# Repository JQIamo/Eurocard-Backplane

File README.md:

# Eurocard-Backplane

A customized backplane for the JQI Eurocard racks.

This repository also includes a "starter" schematic/board for compliant modules: `EurocardModule.*` Simply copy and paste this into your project folder (or re-save with a different name into your project), and you're off to the races!

## JQI Eurocard standard

We have made our backplane standard compliant with the Toptica backplane -- ie, Toptica modules should work in the JQI rack (and vice versa). However, double-check to make sure there aren't conflicting GPIO signal lines!

Compliant modules should follow the backplane standard (see link below to backplane pinout, or check out the starter schematic in this repository). Here are a few other guidlines that should be followed when designing new modules:

* You are responsible for regulating down from `+/-15V` to the voltages you need.
* De-couple your module from the backplane power traces (eg, with a ferrite bead); be careful about introducing additional noise.
* The standard power supply should provide ~ 7 (?) amps of current to the rack at both `+15V` and `-15V`
* If you need higher voltages, use the HV line.
* The backplane will be (!) equipped with a microcontroller and `WIZNET` ethernet adapter.
* SPI chip-select lines (`SPI_CS`) are routed to individual modules (ie, not tied together on the back plane). If you want to use a microcontroller, you can communicate with the backplane MCU this way. You can also use the I2C bus if you wish (`I2C_SDA` and `I2C_SCL`).
* There is a 5V stable reference, provided from an LM399H zener reference on the back plane.

**Resources**:

* [Backplane pinout](https://docs.google.com/spreadsheets/d/1GiwGvO8Z4_M1yfA_NvQcPyxT0hQa0t4iZVfY6wiVYis/edit?usp=sharing)
* ...

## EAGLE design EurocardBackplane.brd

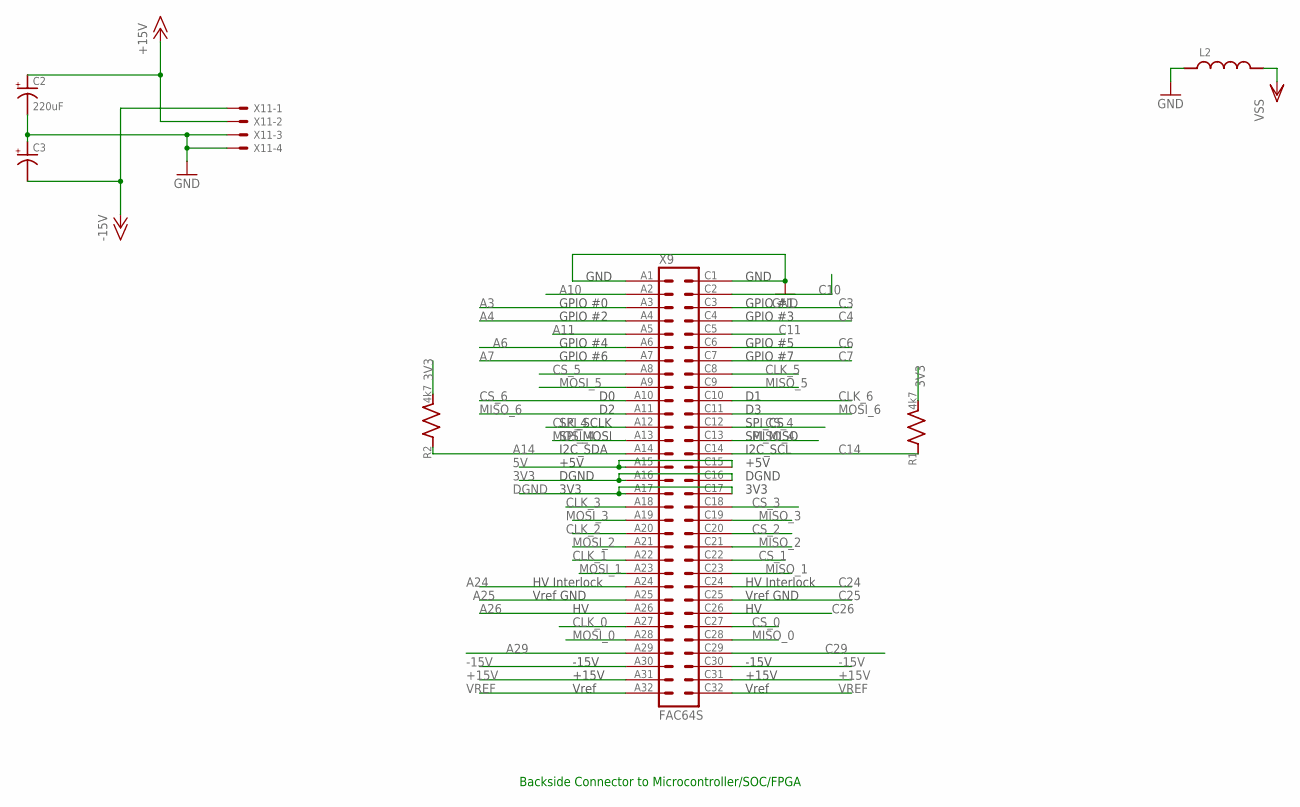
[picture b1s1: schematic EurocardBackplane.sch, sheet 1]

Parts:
C2: 220uF; PANASONIC_F
C3: C_POL_SMDF; PANASONIC_F
L2: L_FERRITE_SMDLFERRITE_0805; R_0805
R1, R2: 4k7; R_0603
X9: FAC64S
X11: 5566-4

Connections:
3V3: R1.P$2 (2), R2.P$2 (2), X9.A16, X9.C16; also elsewhere on the board
5V: X9.A15, X9.C15; also elsewhere on the board
+15V: C2.+, X9.A31, X9.C31, X11.2; also elsewhere on the board
-15V: C3.-, X9.A30, X9.C30, X11.1; also elsewhere on the board
A3: X9.A3; also elsewhere on the board
A4: X9.A4; also elsewhere on the board
A6: X9.A6; also elsewhere on the board
A7: X9.A7; also elsewhere on the board
A10: X9.A2; also elsewhere on the board
A11: X9.A5; also elsewhere on the board
A14: R2.P$1 (1), X9.A14; also elsewhere on the board
A24: X9.A24; also elsewhere on the board
A25: X9.A25; also elsewhere on the board
A26: X9.A26; also elsewhere on the board
A29: X9.A29; also elsewhere on the board
C3: X9.C3; also elsewhere on the board
C4: X9.C4; also elsewhere on the board
C6: X9.C6; also elsewhere on the board
C7: X9.C7; also elsewhere on the board
C10: X9.C2; also elsewhere on the board
C11: X9.C5; also elsewhere on the board
C14: R1.P$1 (1), X9.C14; also elsewhere on the board
C24: X9.C24; also elsewhere on the board
C25: X9.C25; also elsewhere on the board
C26: X9.C26; also elsewhere on the board
C29: X9.C29; also elsewhere on the board
CLK_0: X9.A27; also elsewhere on the board
CLK_1: X9.A22; also elsewhere on the board
CLK_2: X9.A20; also elsewhere on the board
CLK_3: X9.A18; also elsewhere on the board
CLK_4: X9.A12; also elsewhere on the board
CLK_5: X9.C8; also elsewhere on the board
CLK_6: X9.C10; also elsewhere on the board
CS_0: X9.C27; also elsewhere on the board
CS_1: X9.C22; also elsewhere on the board
CS_2: X9.C20; also elsewhere on the board
CS_3: X9.C18; also elsewhere on the board
CS_4: X9.C12; also elsewhere on the board
CS_5: X9.A8; also elsewhere on the board
CS_6: X9.A10; also elsewhere on the board
DGND: X9.A17, X9.C17; also elsewhere on the board
GND: C2.-, C3.+, L2.P$1 (1), X9.A1, X9.C1, X11.3, X11.4; also elsewhere on the board
MISO_0: X9.C28; also elsewhere on the board
MISO_1: X9.C23; also elsewhere on the board
MISO_2: X9.C21; also elsewhere on the board
MISO_3: X9.C19; also elsewhere on the board
MISO_4: X9.C13; also elsewhere on the board
MISO_5: X9.C9; also elsewhere on the board
MISO_6: X9.A11; also elsewhere on the board
MOSI_0: X9.A28; also elsewhere on the board
MOSI_1: X9.A23; also elsewhere on the board
MOSI_2: X9.A21; also elsewhere on the board
MOSI_3: X9.A19; also elsewhere on the board
MOSI_4: X9.A13; also elsewhere on the board
MOSI_5: X9.A9; also elsewhere on the board
MOSI_6: X9.C11; also elsewhere on the board
VREF: X9.A32, X9.C32
VSS: L2.P$2 (2)

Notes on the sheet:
Backside Connector to Microcontroller/SOC/FPGA

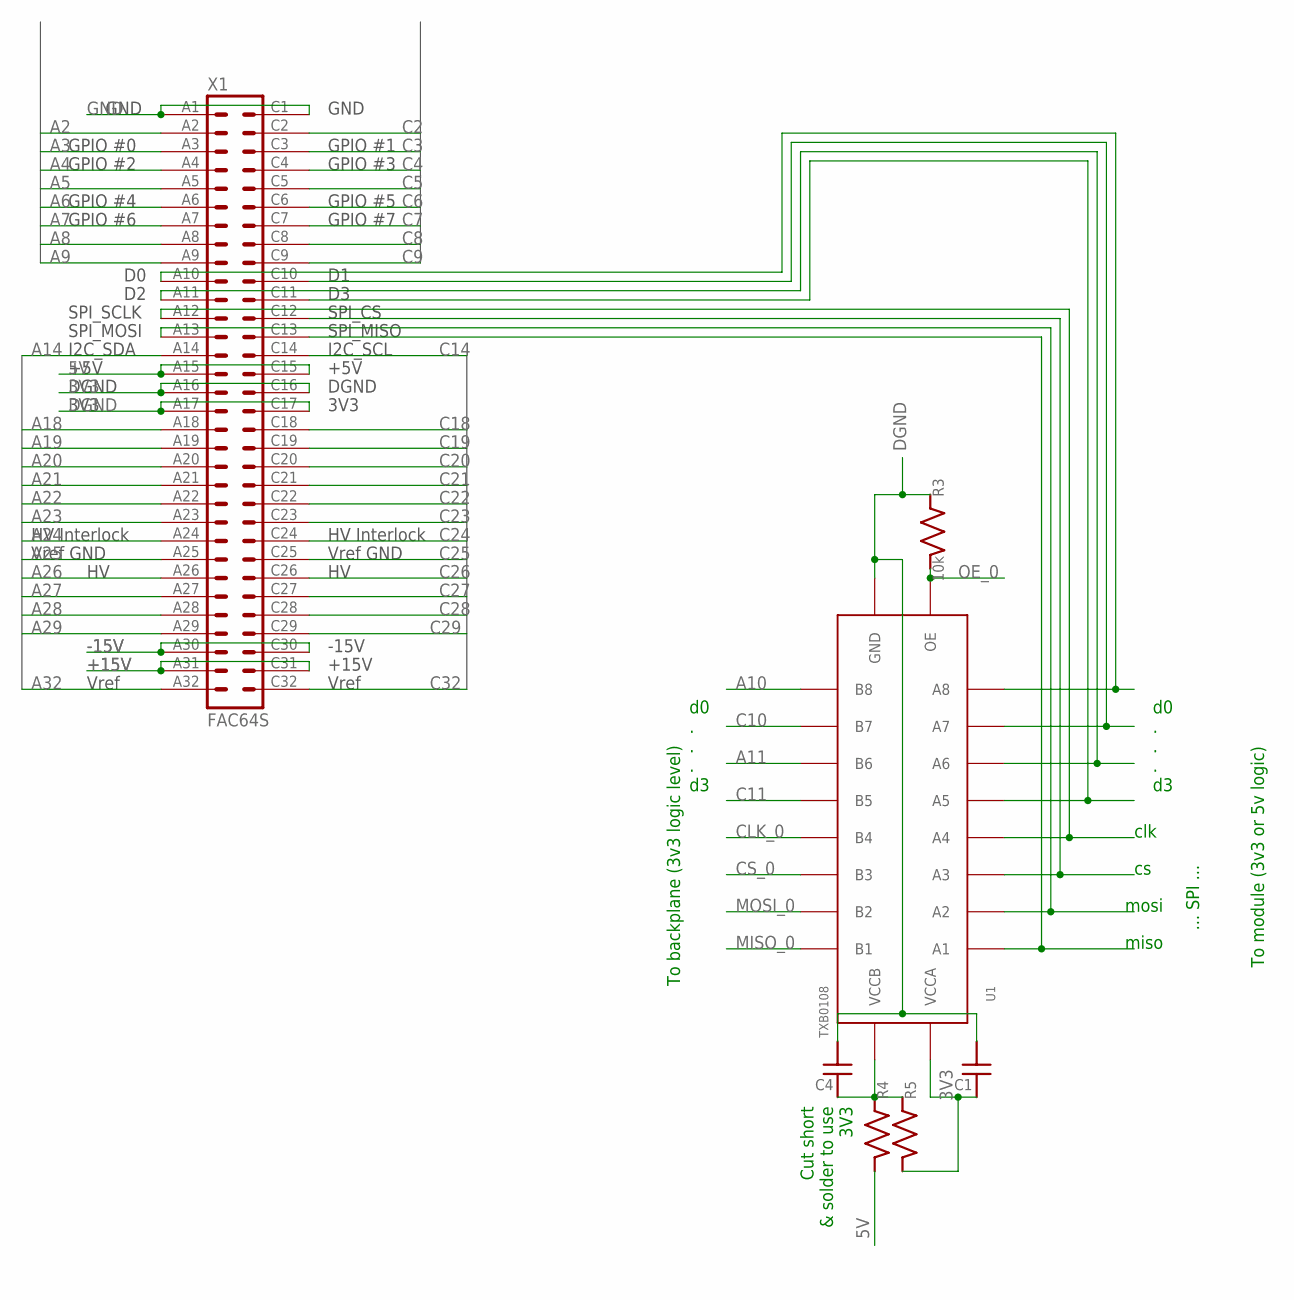
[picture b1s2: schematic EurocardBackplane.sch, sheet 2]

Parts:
C1, C4: C_MLCC_SMDCMLCC_0603; C_MLCC_0603
R3: 10k; R_0603
R4, R5: R_SMDR0603; R_0603
U1: TXB0108; TSSOP20
X1: FAC64S

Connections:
3V3: C1.P$1 (1), R5.P$2 (2), U1.2 (VCCA), X1.A16, X1.C16; also elsewhere on the board
5V: R4.P$2 (2), X1.A15, X1.C15; also elsewhere on the board
+15V: X1.A31, X1.C31; also elsewhere on the board
-15V: X1.A30, X1.C30; also elsewhere on the board
A2: X1.A2; also elsewhere on the board
A3: X1.A3; also elsewhere on the board
A4: X1.A4; also elsewhere on the board
A5: X1.A5; also elsewhere on the board
A6: X1.A6; also elsewhere on the board
A7: X1.A7; also elsewhere on the board
A8: X1.A8; also elsewhere on the board
A9: X1.A9; also elsewhere on the board
A10: U1.12 (B8); also elsewhere on the board
A11: U1.14 (B6); also elsewhere on the board
A14: X1.A14; also elsewhere on the board
A18: X1.A18; also elsewhere on the board
A19: X1.A19; also elsewhere on the board
A20: X1.A20; also elsewhere on the board
A21: X1.A21; also elsewhere on the board
A22: X1.A22; also elsewhere on the board
A23: X1.A23; also elsewhere on the board
A24: X1.A24; also elsewhere on the board
A25: X1.A25; also elsewhere on the board
A26: X1.A26; also elsewhere on the board
A27: X1.A27; also elsewhere on the board
A28: X1.A28; also elsewhere on the board
A29: X1.A29; also elsewhere on the board
A32: X1.A32; also elsewhere on the board
C2: X1.C2; also elsewhere on the board
C3: X1.C3; also elsewhere on the board
C4: X1.C4; also elsewhere on the board
C5: X1.C5; also elsewhere on the board
C6: X1.C6; also elsewhere on the board
C7: X1.C7; also elsewhere on the board
C8: X1.C8; also elsewhere on the board
C9: X1.C9; also elsewhere on the board
C10: U1.13 (B7); also elsewhere on the board
C11: U1.15 (B5); also elsewhere on the board
C14: X1.C14; also elsewhere on the board
C18: X1.C18; also elsewhere on the board
C19: X1.C19; also elsewhere on the board
C20: X1.C20; also elsewhere on the board
C21: X1.C21; also elsewhere on the board
C22: X1.C22; also elsewhere on the board
C23: X1.C23; also elsewhere on the board
C24: X1.C24; also elsewhere on the board
C25: X1.C25; also elsewhere on the board
C26: X1.C26; also elsewhere on the board
C27: X1.C27; also elsewhere on the board
C28: X1.C28; also elsewhere on the board
C29: X1.C29; also elsewhere on the board
C32: X1.C32; also elsewhere on the board
CLK_0: U1.16 (B4); also elsewhere on the board
CS_0: U1.17 (B3); also elsewhere on the board
DGND: C1.P$2 (2), C4.P$2 (2), R3.P$1 (1), U1.11 (GND), X1.A17, X1.C17; also elsewhere on the board
GND: X1.A1, X1.C1; also elsewhere on the board
MISO_0: U1.20 (B1); also elsewhere on the board
MOSI_0: U1.18 (B2); also elsewhere on the board
unnamed: U1.9 (A8), X1.A10
unnamed: U1.8 (A7), X1.C10
unnamed: U1.7 (A6), X1.A11
unnamed: U1.6 (A5), X1.C11
unnamed: U1.5 (A4), X1.A12
unnamed: U1.4 (A3), X1.C12
unnamed: U1.3 (A2), X1.A13
unnamed: U1.1 (A1), X1.C13
unnamed: C4.P$1 (1), R4.P$1 (1), R5.P$1 (1), U1.19 (VCCB)
OE_0: R3.P$2 (2), U1.10 (OE)

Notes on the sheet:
d0 . . . d3
To backplane (3v3 logic level)
To module (3v3 or 5v logic)
clk
mosi
miso
... SPI ...
Cut short & solder to use 3V3

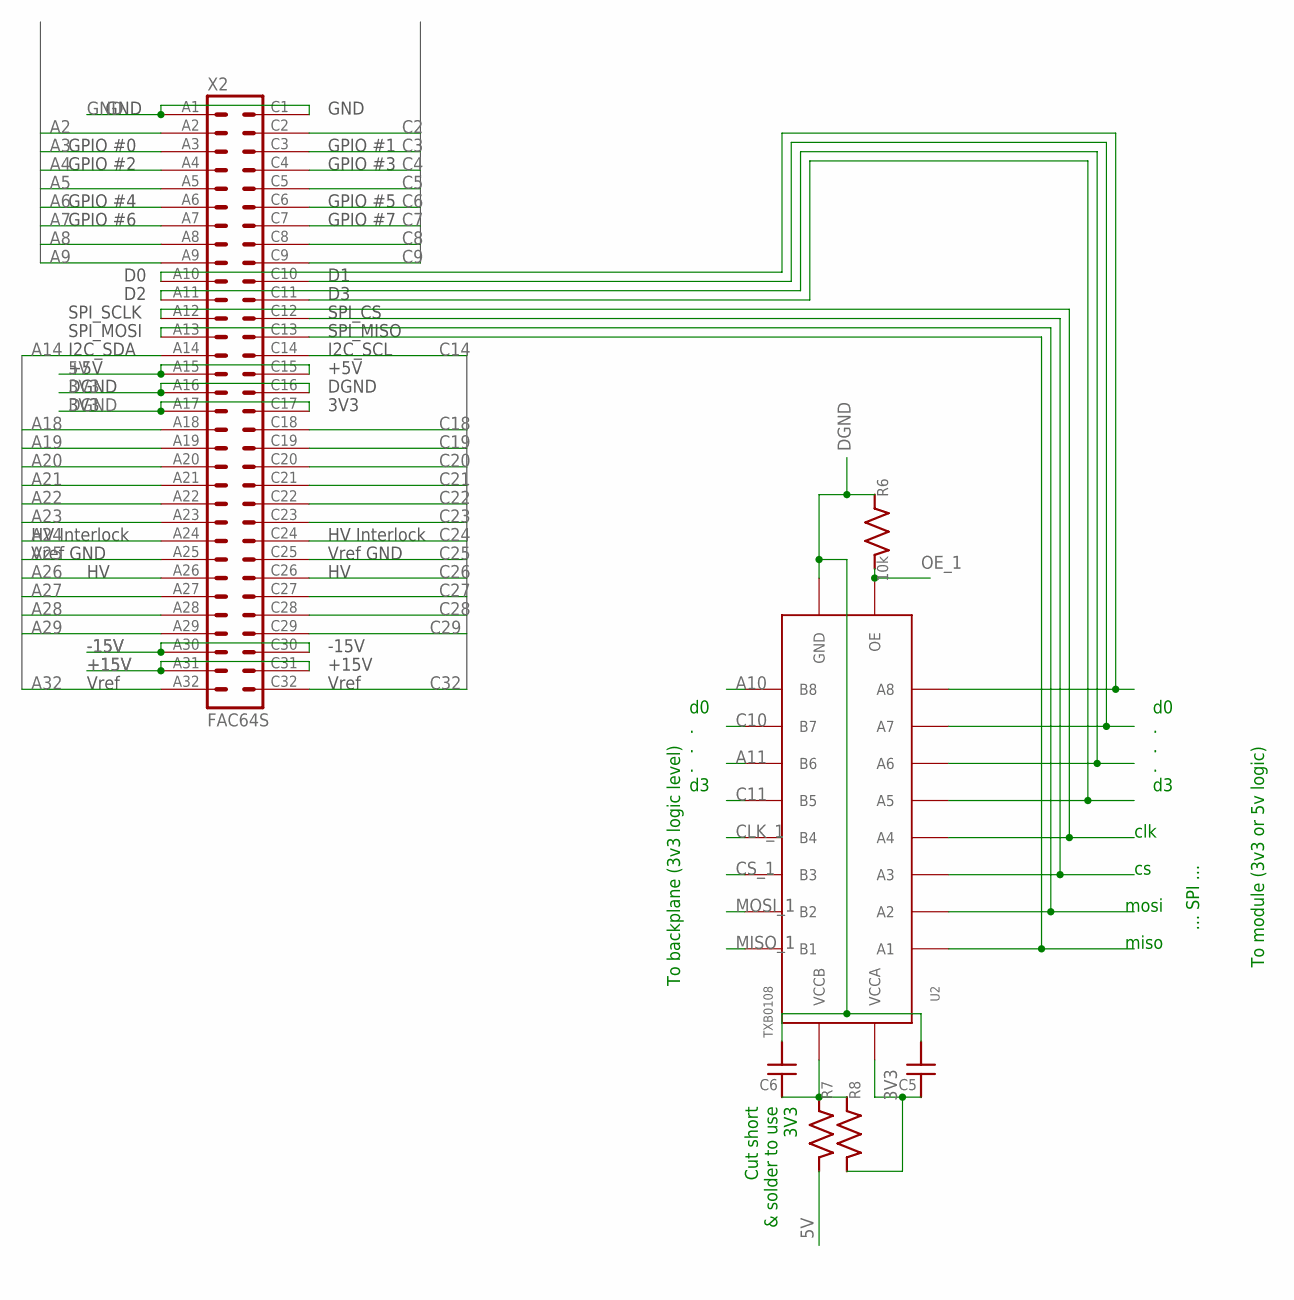
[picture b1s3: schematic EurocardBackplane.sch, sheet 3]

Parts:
C5, C6: C_MLCC_SMDCMLCC_0603; C_MLCC_0603
R6: 10k; R_0603
R7, R8: R_SMDR0603; R_0603
U2: TXB0108; TSSOP20
X2: FAC64S

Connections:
3V3: C5.P$1 (1), R8.P$2 (2), U2.2 (VCCA), X2.A16, X2.C16; also elsewhere on the board
5V: R7.P$2 (2), X2.A15, X2.C15; also elsewhere on the board
+15V: X2.A31, X2.C31; also elsewhere on the board
-15V: X2.A30, X2.C30; also elsewhere on the board
A2: X2.A2; also elsewhere on the board
A3: X2.A3; also elsewhere on the board
A4: X2.A4; also elsewhere on the board
A5: X2.A5; also elsewhere on the board
A6: X2.A6; also elsewhere on the board
A7: X2.A7; also elsewhere on the board
A8: X2.A8; also elsewhere on the board
A9: X2.A9; also elsewhere on the board
A10: U2.12 (B8); also elsewhere on the board
A11: U2.14 (B6); also elsewhere on the board
A14: X2.A14; also elsewhere on the board
A18: X2.A18; also elsewhere on the board
A19: X2.A19; also elsewhere on the board
A20: X2.A20; also elsewhere on the board
A21: X2.A21; also elsewhere on the board
A22: X2.A22; also elsewhere on the board
A23: X2.A23; also elsewhere on the board
A24: X2.A24; also elsewhere on the board
A25: X2.A25; also elsewhere on the board
A26: X2.A26; also elsewhere on the board
A27: X2.A27; also elsewhere on the board
A28: X2.A28; also elsewhere on the board
A29: X2.A29; also elsewhere on the board
A32: X2.A32; also elsewhere on the board
C2: X2.C2; also elsewhere on the board
C3: X2.C3; also elsewhere on the board
C4: X2.C4; also elsewhere on the board
C5: X2.C5; also elsewhere on the board
C6: X2.C6; also elsewhere on the board
C7: X2.C7; also elsewhere on the board
C8: X2.C8; also elsewhere on the board
C9: X2.C9; also elsewhere on the board
C10: U2.13 (B7); also elsewhere on the board
C11: U2.15 (B5); also elsewhere on the board
C14: X2.C14; also elsewhere on the board
C18: X2.C18; also elsewhere on the board
C19: X2.C19; also elsewhere on the board
C20: X2.C20; also elsewhere on the board
C21: X2.C21; also elsewhere on the board
C22: X2.C22; also elsewhere on the board
C23: X2.C23; also elsewhere on the board
C24: X2.C24; also elsewhere on the board
C25: X2.C25; also elsewhere on the board
C26: X2.C26; also elsewhere on the board
C27: X2.C27; also elsewhere on the board
C28: X2.C28; also elsewhere on the board
C29: X2.C29; also elsewhere on the board
C32: X2.C32; also elsewhere on the board
CLK_1: U2.16 (B4); also elsewhere on the board
CS_1: U2.17 (B3); also elsewhere on the board
DGND: C5.P$2 (2), C6.P$2 (2), R6.P$1 (1), U2.11 (GND), X2.A17, X2.C17; also elsewhere on the board
GND: X2.A1, X2.C1; also elsewhere on the board
MISO_1: U2.20 (B1); also elsewhere on the board
MOSI_1: U2.18 (B2); also elsewhere on the board
unnamed: U2.9 (A8), X2.A10
unnamed: U2.8 (A7), X2.C10
unnamed: U2.7 (A6), X2.A11
unnamed: U2.6 (A5), X2.C11
unnamed: U2.5 (A4), X2.A12
unnamed: U2.4 (A3), X2.C12
unnamed: U2.3 (A2), X2.A13
unnamed: U2.1 (A1), X2.C13
unnamed: C6.P$1 (1), R7.P$1 (1), R8.P$1 (1), U2.19 (VCCB)
OE_1: R6.P$2 (2), U2.10 (OE)

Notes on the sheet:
d0 . . . d3
To backplane (3v3 logic level)
To module (3v3 or 5v logic)
clk
mosi
miso
... SPI ...
Cut short & solder to use 3V3

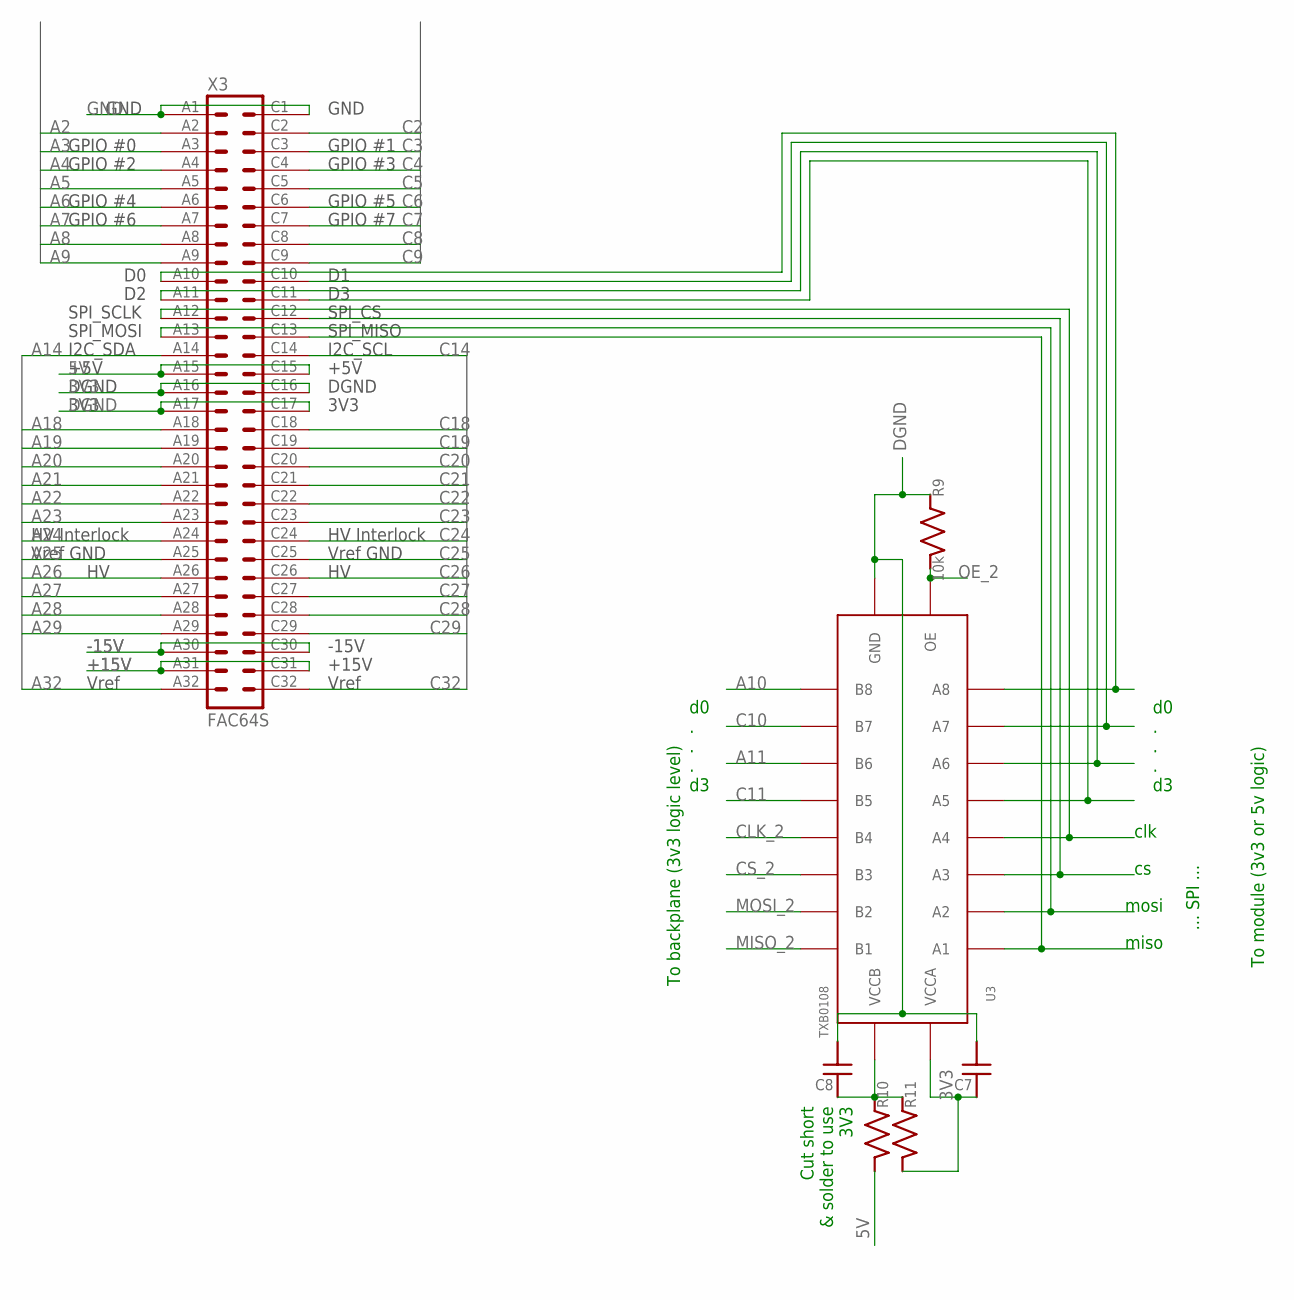
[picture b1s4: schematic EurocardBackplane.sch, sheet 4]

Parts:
C7, C8: C_MLCC_SMDCMLCC_0603; C_MLCC_0603
R9: 10k; R_0603
R10, R11: R_SMDR0603; R_0603
U3: TXB0108; TSSOP20
X3: FAC64S

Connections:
3V3: C7.P$1 (1), R11.P$2 (2), U3.2 (VCCA), X3.A16, X3.C16; also elsewhere on the board
5V: R10.P$2 (2), X3.A15, X3.C15; also elsewhere on the board
+15V: X3.A31, X3.C31; also elsewhere on the board
-15V: X3.A30, X3.C30; also elsewhere on the board
A2: X3.A2; also elsewhere on the board
A3: X3.A3; also elsewhere on the board
A4: X3.A4; also elsewhere on the board
A5: X3.A5; also elsewhere on the board
A6: X3.A6; also elsewhere on the board
A7: X3.A7; also elsewhere on the board
A8: X3.A8; also elsewhere on the board
A9: X3.A9; also elsewhere on the board
A10: U3.12 (B8); also elsewhere on the board
A11: U3.14 (B6); also elsewhere on the board
A14: X3.A14; also elsewhere on the board
A18: X3.A18; also elsewhere on the board
A19: X3.A19; also elsewhere on the board
A20: X3.A20; also elsewhere on the board
A21: X3.A21; also elsewhere on the board
A22: X3.A22; also elsewhere on the board
A23: X3.A23; also elsewhere on the board
A24: X3.A24; also elsewhere on the board
A25: X3.A25; also elsewhere on the board
A26: X3.A26; also elsewhere on the board
A27: X3.A27; also elsewhere on the board
A28: X3.A28; also elsewhere on the board
A29: X3.A29; also elsewhere on the board
A32: X3.A32; also elsewhere on the board
C2: X3.C2; also elsewhere on the board
C3: X3.C3; also elsewhere on the board
C4: X3.C4; also elsewhere on the board
C5: X3.C5; also elsewhere on the board
C6: X3.C6; also elsewhere on the board
C7: X3.C7; also elsewhere on the board
C8: X3.C8; also elsewhere on the board
C9: X3.C9; also elsewhere on the board
C10: U3.13 (B7); also elsewhere on the board
C11: U3.15 (B5); also elsewhere on the board
C14: X3.C14; also elsewhere on the board
C18: X3.C18; also elsewhere on the board
C19: X3.C19; also elsewhere on the board
C20: X3.C20; also elsewhere on the board
C21: X3.C21; also elsewhere on the board
C22: X3.C22; also elsewhere on the board
C23: X3.C23; also elsewhere on the board
C24: X3.C24; also elsewhere on the board
C25: X3.C25; also elsewhere on the board
C26: X3.C26; also elsewhere on the board
C27: X3.C27; also elsewhere on the board
C28: X3.C28; also elsewhere on the board
C29: X3.C29; also elsewhere on the board
C32: X3.C32; also elsewhere on the board
CLK_2: U3.16 (B4); also elsewhere on the board
CS_2: U3.17 (B3); also elsewhere on the board
DGND: C7.P$2 (2), C8.P$2 (2), R9.P$1 (1), U3.11 (GND), X3.A17, X3.C17; also elsewhere on the board
GND: X3.A1, X3.C1; also elsewhere on the board
MISO_2: U3.20 (B1); also elsewhere on the board
MOSI_2: U3.18 (B2); also elsewhere on the board
unnamed: U3.9 (A8), X3.A10
unnamed: U3.8 (A7), X3.C10
unnamed: U3.7 (A6), X3.A11
unnamed: U3.6 (A5), X3.C11
unnamed: U3.5 (A4), X3.A12
unnamed: U3.4 (A3), X3.C12
unnamed: U3.3 (A2), X3.A13
unnamed: U3.1 (A1), X3.C13
unnamed: C8.P$1 (1), R10.P$1 (1), R11.P$1 (1), U3.19 (VCCB)
OE_2: R9.P$2 (2), U3.10 (OE)

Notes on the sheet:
d0 . . . d3
To backplane (3v3 logic level)
To module (3v3 or 5v logic)
clk
mosi
miso
... SPI ...
Cut short & solder to use 3V3

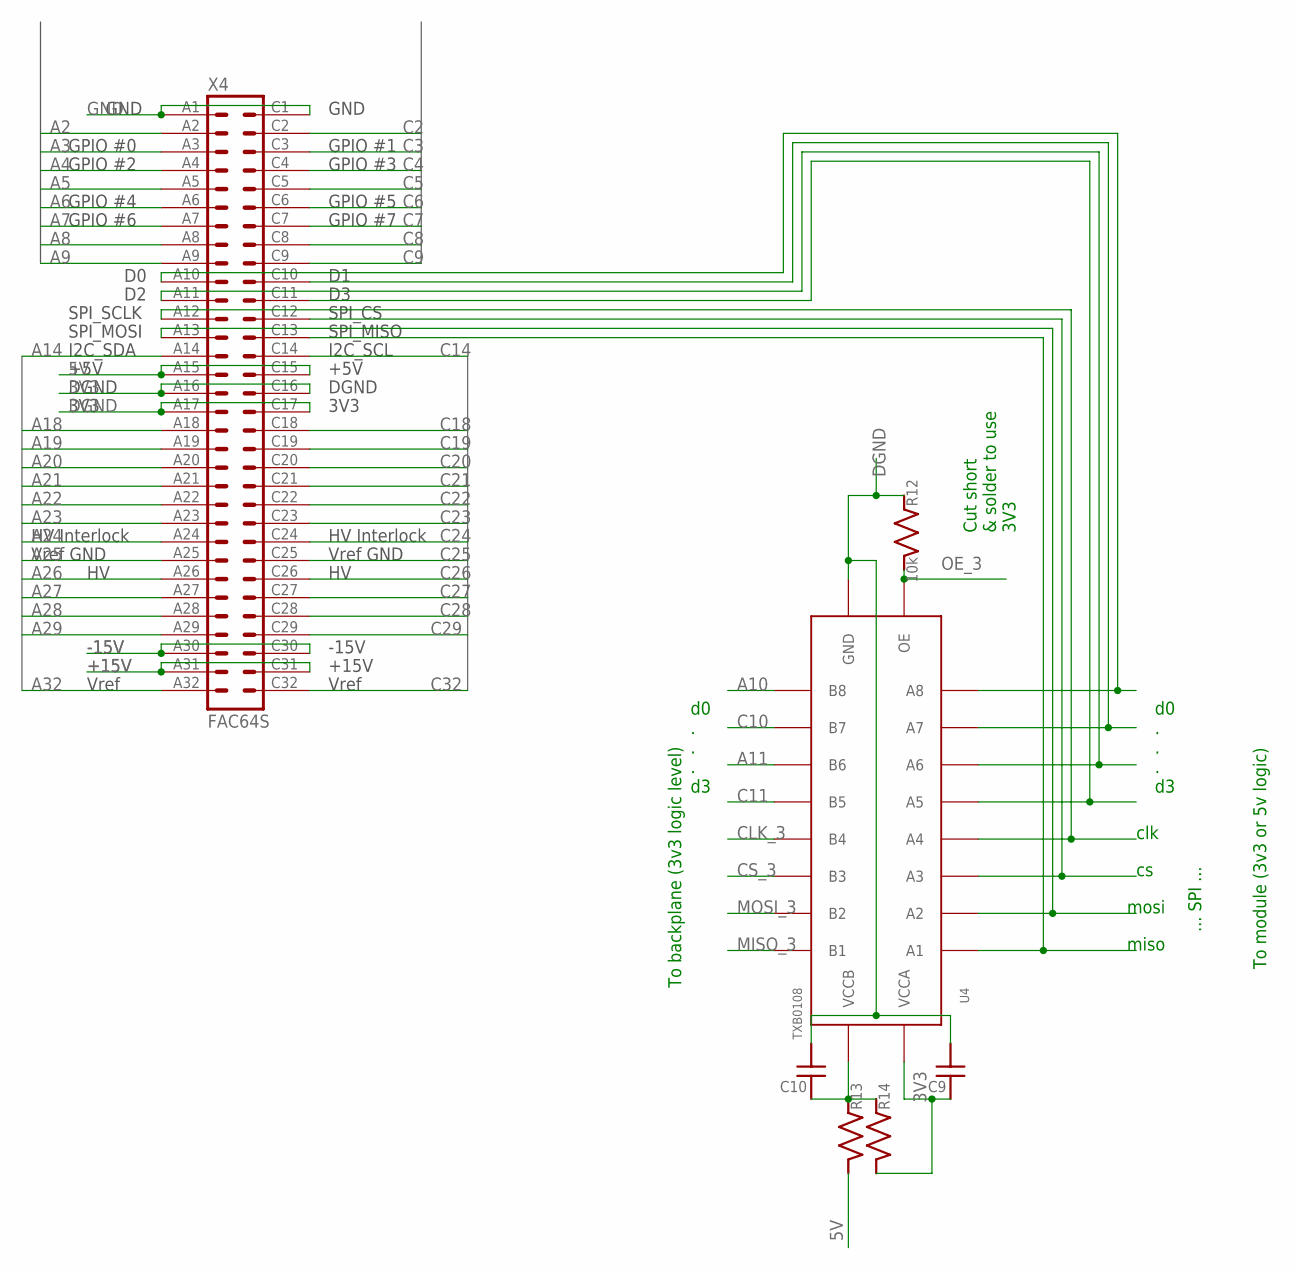
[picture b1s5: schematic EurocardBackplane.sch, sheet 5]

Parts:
C9, C10: C_MLCC_SMDCMLCC_0603; C_MLCC_0603
R12: 10k; R_0603
R13, R14: R_SMDR0603; R_0603
U4: TXB0108; TSSOP20
X4: FAC64S

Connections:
3V3: C9.P$1 (1), R14.P$2 (2), U4.2 (VCCA), X4.A16, X4.C16; also elsewhere on the board
5V: R13.P$2 (2), X4.A15, X4.C15; also elsewhere on the board
+15V: X4.A31, X4.C31; also elsewhere on the board
-15V: X4.A30, X4.C30; also elsewhere on the board
A2: X4.A2; also elsewhere on the board
A3: X4.A3; also elsewhere on the board
A4: X4.A4; also elsewhere on the board
A5: X4.A5; also elsewhere on the board
A6: X4.A6; also elsewhere on the board
A7: X4.A7; also elsewhere on the board
A8: X4.A8; also elsewhere on the board
A9: X4.A9; also elsewhere on the board
A10: U4.12 (B8); also elsewhere on the board
A11: U4.14 (B6); also elsewhere on the board
A14: X4.A14; also elsewhere on the board
A18: X4.A18; also elsewhere on the board
A19: X4.A19; also elsewhere on the board
A20: X4.A20; also elsewhere on the board
A21: X4.A21; also elsewhere on the board
A22: X4.A22; also elsewhere on the board
A23: X4.A23; also elsewhere on the board
A24: X4.A24; also elsewhere on the board
A25: X4.A25; also elsewhere on the board
A26: X4.A26; also elsewhere on the board
A27: X4.A27; also elsewhere on the board
A28: X4.A28; also elsewhere on the board
A29: X4.A29; also elsewhere on the board
A32: X4.A32; also elsewhere on the board
C2: X4.C2; also elsewhere on the board
C3: X4.C3; also elsewhere on the board
C4: X4.C4; also elsewhere on the board
C5: X4.C5; also elsewhere on the board
C6: X4.C6; also elsewhere on the board
C7: X4.C7; also elsewhere on the board
C8: X4.C8; also elsewhere on the board
C9: X4.C9; also elsewhere on the board
C10: U4.13 (B7); also elsewhere on the board
C11: U4.15 (B5); also elsewhere on the board
C14: X4.C14; also elsewhere on the board
C18: X4.C18; also elsewhere on the board
C19: X4.C19; also elsewhere on the board
C20: X4.C20; also elsewhere on the board
C21: X4.C21; also elsewhere on the board
C22: X4.C22; also elsewhere on the board
C23: X4.C23; also elsewhere on the board
C24: X4.C24; also elsewhere on the board
C25: X4.C25; also elsewhere on the board
C26: X4.C26; also elsewhere on the board
C27: X4.C27; also elsewhere on the board
C28: X4.C28; also elsewhere on the board
C29: X4.C29; also elsewhere on the board
C32: X4.C32; also elsewhere on the board
CLK_3: U4.16 (B4); also elsewhere on the board
CS_3: U4.17 (B3); also elsewhere on the board
DGND: C9.P$2 (2), C10.P$2 (2), R12.P$1 (1), U4.11 (GND), X4.A17, X4.C17; also elsewhere on the board
GND: X4.A1, X4.C1; also elsewhere on the board
MISO_3: U4.20 (B1); also elsewhere on the board
MOSI_3: U4.18 (B2); also elsewhere on the board
unnamed: U4.9 (A8), X4.A10
unnamed: U4.8 (A7), X4.C10
unnamed: U4.7 (A6), X4.A11
unnamed: U4.6 (A5), X4.C11
unnamed: U4.5 (A4), X4.A12
unnamed: U4.4 (A3), X4.C12
unnamed: U4.3 (A2), X4.A13
unnamed: U4.1 (A1), X4.C13
unnamed: C10.P$1 (1), R13.P$1 (1), R14.P$1 (1), U4.19 (VCCB)
OE_3: R12.P$2 (2), U4.10 (OE)

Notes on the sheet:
d0 . . . d3
To backplane (3v3 logic level)
To module (3v3 or 5v logic)
clk
mosi
miso
... SPI ...
Cut short & solder to use 3V3

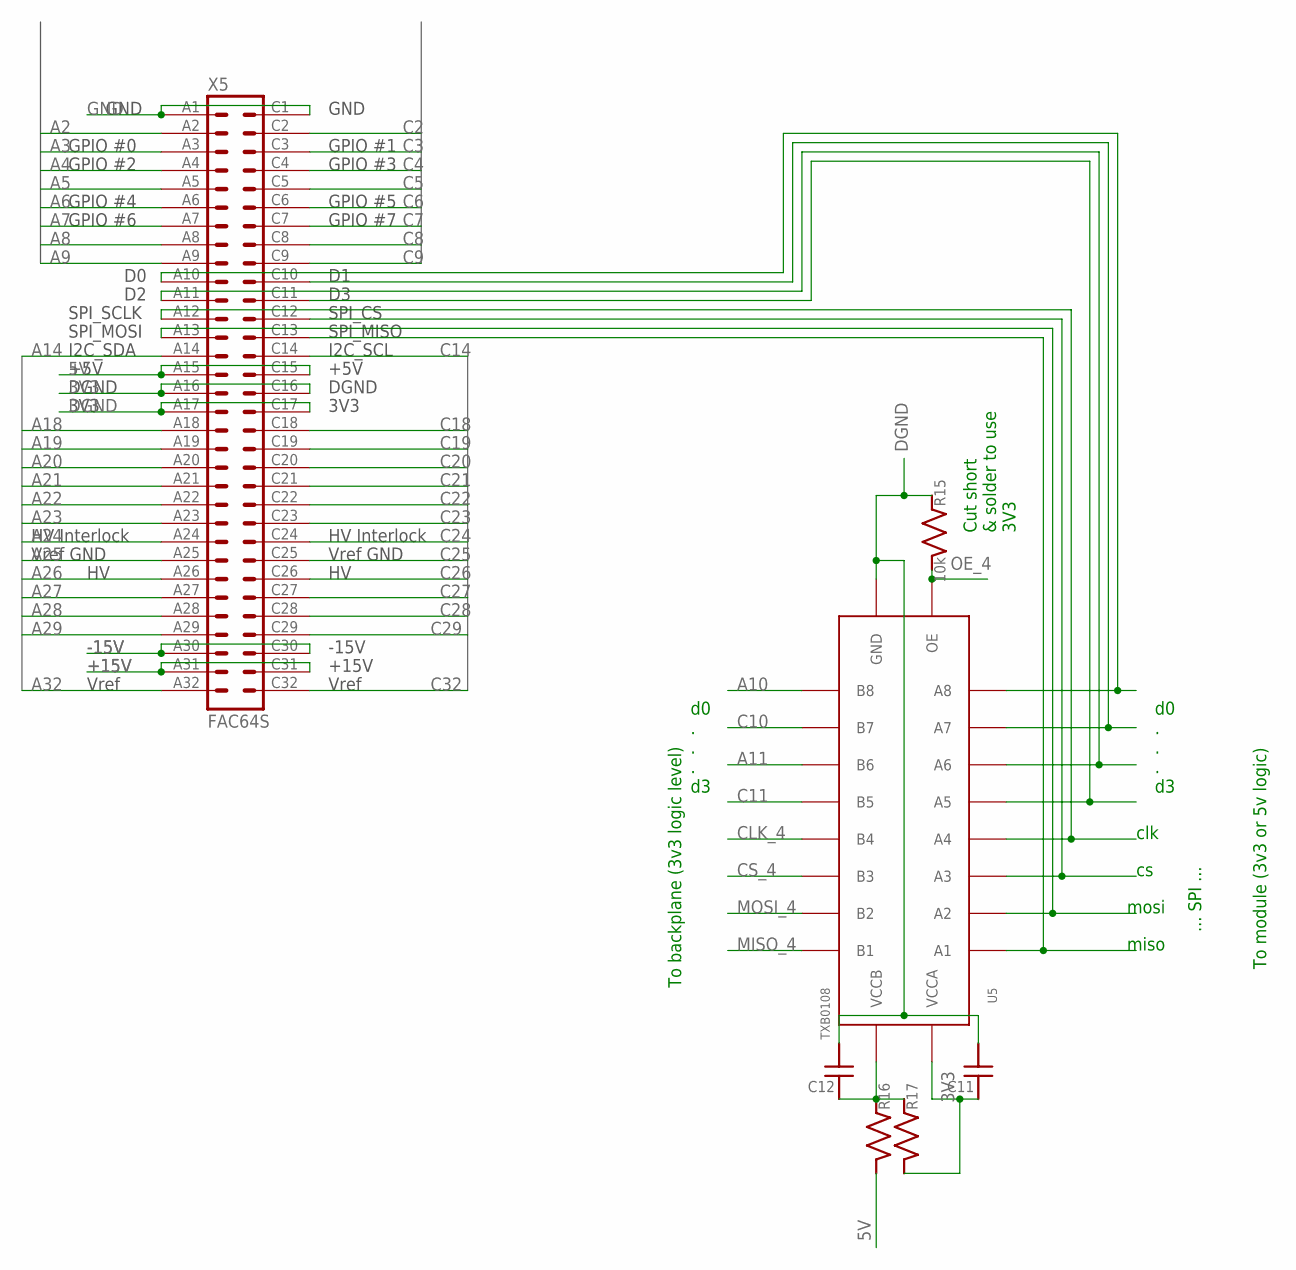
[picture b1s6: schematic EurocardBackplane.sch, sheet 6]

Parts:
C11, C12: C_MLCC_SMDCMLCC_0603; C_MLCC_0603
R15: 10k; R_0603
R16, R17: R_SMDR0603; R_0603
U5: TXB0108; TSSOP20
X5: FAC64S

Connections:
3V3: C11.P$1 (1), R17.P$2 (2), U5.2 (VCCA), X5.A16, X5.C16; also elsewhere on the board
5V: R16.P$2 (2), X5.A15, X5.C15; also elsewhere on the board
+15V: X5.A31, X5.C31; also elsewhere on the board
-15V: X5.A30, X5.C30; also elsewhere on the board
A2: X5.A2; also elsewhere on the board
A3: X5.A3; also elsewhere on the board
A4: X5.A4; also elsewhere on the board
A5: X5.A5; also elsewhere on the board
A6: X5.A6; also elsewhere on the board
A7: X5.A7; also elsewhere on the board
A8: X5.A8; also elsewhere on the board
A9: X5.A9; also elsewhere on the board
A10: U5.12 (B8); also elsewhere on the board
A11: U5.14 (B6); also elsewhere on the board
A14: X5.A14; also elsewhere on the board
A18: X5.A18; also elsewhere on the board
A19: X5.A19; also elsewhere on the board
A20: X5.A20; also elsewhere on the board
A21: X5.A21; also elsewhere on the board
A22: X5.A22; also elsewhere on the board
A23: X5.A23; also elsewhere on the board
A24: X5.A24; also elsewhere on the board
A25: X5.A25; also elsewhere on the board
A26: X5.A26; also elsewhere on the board
A27: X5.A27; also elsewhere on the board
A28: X5.A28; also elsewhere on the board
A29: X5.A29; also elsewhere on the board
A32: X5.A32; also elsewhere on the board
C2: X5.C2; also elsewhere on the board
C3: X5.C3; also elsewhere on the board
C4: X5.C4; also elsewhere on the board
C5: X5.C5; also elsewhere on the board
C6: X5.C6; also elsewhere on the board
C7: X5.C7; also elsewhere on the board
C8: X5.C8; also elsewhere on the board
C9: X5.C9; also elsewhere on the board
C10: U5.13 (B7); also elsewhere on the board
C11: U5.15 (B5); also elsewhere on the board
C14: X5.C14; also elsewhere on the board
C18: X5.C18; also elsewhere on the board
C19: X5.C19; also elsewhere on the board
C20: X5.C20; also elsewhere on the board
C21: X5.C21; also elsewhere on the board
C22: X5.C22; also elsewhere on the board
C23: X5.C23; also elsewhere on the board
C24: X5.C24; also elsewhere on the board
C25: X5.C25; also elsewhere on the board
C26: X5.C26; also elsewhere on the board
C27: X5.C27; also elsewhere on the board
C28: X5.C28; also elsewhere on the board
C29: X5.C29; also elsewhere on the board
C32: X5.C32; also elsewhere on the board
CLK_4: U5.16 (B4); also elsewhere on the board
CS_4: U5.17 (B3); also elsewhere on the board
DGND: C11.P$2 (2), C12.P$2 (2), R15.P$1 (1), U5.11 (GND), X5.A17, X5.C17; also elsewhere on the board
GND: X5.A1, X5.C1; also elsewhere on the board
MISO_4: U5.20 (B1); also elsewhere on the board
MOSI_4: U5.18 (B2); also elsewhere on the board
unnamed: U5.9 (A8), X5.A10
unnamed: U5.8 (A7), X5.C10
unnamed: U5.7 (A6), X5.A11
unnamed: U5.6 (A5), X5.C11
unnamed: U5.5 (A4), X5.A12
unnamed: U5.4 (A3), X5.C12
unnamed: U5.3 (A2), X5.A13
unnamed: U5.1 (A1), X5.C13
unnamed: C12.P$1 (1), R16.P$1 (1), R17.P$1 (1), U5.19 (VCCB)
OE_4: R15.P$2 (2), U5.10 (OE)

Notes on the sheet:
d0 . . . d3
To backplane (3v3 logic level)
To module (3v3 or 5v logic)
clk
mosi
miso
... SPI ...
Cut short & solder to use 3V3
